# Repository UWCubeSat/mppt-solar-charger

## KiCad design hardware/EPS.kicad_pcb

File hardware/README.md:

# MPPTSolarCharger

A Maximum Power Point Tracking battery charger circuit for testing solar panels and developing efficient battery management systems.

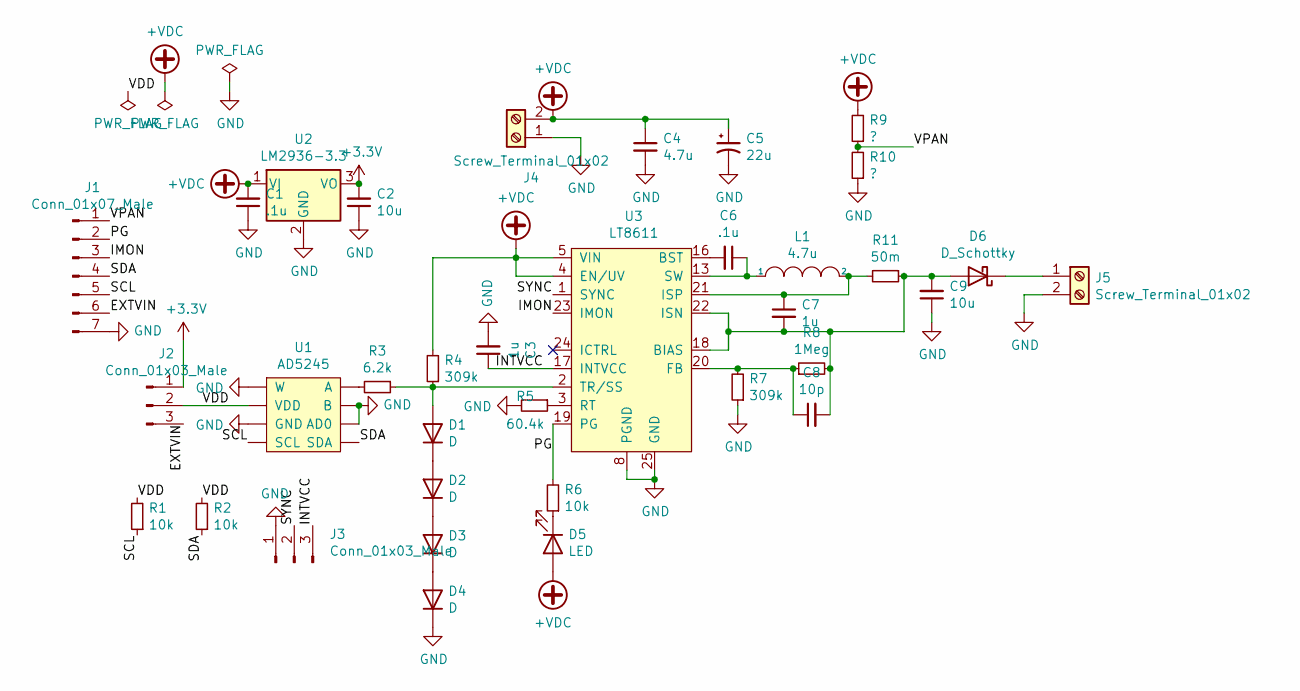
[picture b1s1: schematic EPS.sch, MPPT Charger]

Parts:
C1, C6: .1u; C_0805_2012Metric_Pad1.15x1.40mm_HandSolder
C2, C9: 10u; C_0805_2012Metric_Pad1.15x1.40mm_HandSolder
C3, C7: 1u; C_0805_2012Metric_Pad1.15x1.40mm_HandSolder
C4: 4.7u; C_0805_2012Metric_Pad1.15x1.40mm_HandSolder
C5: 22u; CP_Radial_D6.3mm_P2.50mm
C8: 10p; C_0805_2012Metric_Pad1.15x1.40mm_HandSolder
D1, D2, D3, D4: D; D_SOD-123
D5: LED; LED_0805_2012Metric_Pad1.15x1.40mm_HandSolder
D6: D_Schottky; D_SOD-128
J1: Conn_01x07_Male; PinHeader_1x07_P2.54mm_Vertical
J2, J3: Conn_01x03_Male; PinHeader_1x03_P2.54mm_Vertical
J4, J5: Screw_Terminal_01x02; TerminalBlock_Phoenix_PT-1,5-2-3.5-H_1x02_P3.50mm_Horizontal
L1: 4.7u; BWVS00606045
R1, R2, R6: 10k; R_0805_2012Metric_Pad1.15x1.40mm_HandSolder
R3: 6.2k; R_0805_2012Metric_Pad1.15x1.40mm_HandSolder
R4, R7: 309k; R_0805_2012Metric_Pad1.15x1.40mm_HandSolder
R5: 60.4k; R_0805_2012Metric_Pad1.15x1.40mm_HandSolder
R8: 1Meg; R_0805_2012Metric_Pad1.15x1.40mm_HandSolder
R9, R10: ?; R_0805_2012Metric_Pad1.15x1.40mm_HandSolder
R11: 50m; R_2512_6332Metric_Pad1.52x3.35mm_HandSolder
U1: AD5245; SOT-23-8
U2: LM2936-3.3; SOT-223-3_TabPin2
U3: LT8611; 24-QFN_3x5

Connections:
+3V3: C2.2, J2.1, U2.3 (VO)
+VDC: C1.2, C4.1, C5.1, D5.2 (A), J4.2, R4.2, R9.2, U2.1 (VI), U3.4 (EN/UV), U3.5 (VIN), U3.6 (VIN)
/EXTVIN: J1.6, J2.3
/IMON: J1.3, U3.23 (IMON)
/INTVCC: C3.1, J3.3, U3.17 (INTVCC)
/PG: J1.2, R6.2, U3.19 (PG)
/SCL: J1.5, R1.1, U1.4 (SCL)
/SDA: J1.4, R2.1, U1.5 (SDA)
/SYNC: J3.2, U3.1 (SYNC)
/VDD: J2.2, R1.2, R2.2, U1.2 (VDD)
/VPAN: J1.1, R9.1, R10.2
GND: C1.1, C2.1, C3.2, C4.2, C5.2, C9.1, D4.1 (K), J1.7, J3.1, J4.1, J5.2, R5.2, R7.1, R10.1, U1.1 (W), U1.3 (GND), U1.6 (AD0), U1.7 (B), U2.2 (GND), U3.7 (PGND), U3.8 (PGND), U3.9 (NC), U3.10 (NC), U3.11 (NC), U3.12 (NC), U3.25 (GND)
unnamed: C6.1, L1.1, U3.13 (SW), U3.14 (SW), U3.15 (SW)
unnamed: C6.2, U3.16 (BST)
unnamed: C7.1, L1.2, R11.2, U3.21 (ISP)
unnamed: C7.2, C8.2, C9.2, D6.2 (A), R8.2, R11.1, U3.18 (BIAS), U3.22 (ISN)
unnamed: C8.1, R7.2, R8.1, U3.20 (FB)
unnamed: D1.1 (K), D2.2 (A)
unnamed: D1.2 (A), R3.1, R4.1, U3.2 (TR/SS)
unnamed: D2.1 (K), D3.2 (A)
unnamed: D3.1 (K), D4.2 (A)
unnamed: D5.1 (K), R6.1
unnamed: D6.1 (K), J5.1
unnamed: R3.2, U1.8 (A)
unnamed: R5.1, U3.3 (RT)

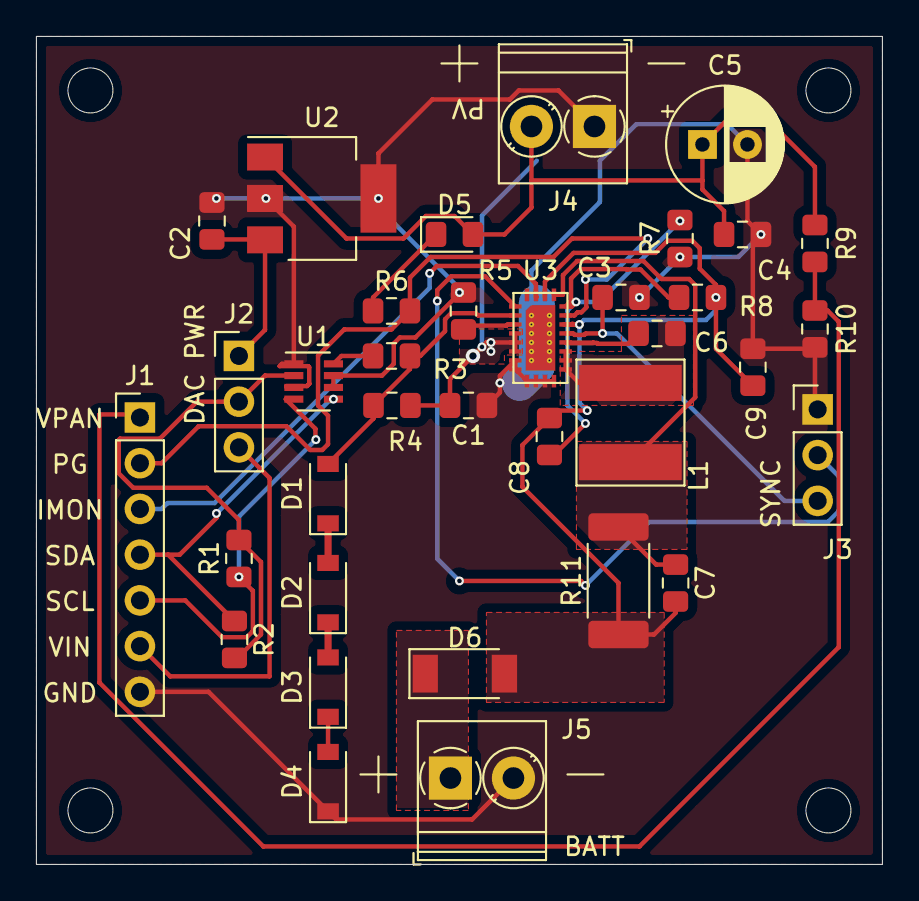
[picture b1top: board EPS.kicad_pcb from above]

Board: 2 copper layers, 47.0 x 46.0 mm, 35 parts (0 on the bottom side), 25 nets.

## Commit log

2020-11-28 Added LT8611 MPPT Eval Schematic
2020-11-28 Rename MTTP.asc to MPPT.asc
2020-11-28 Modified schematic to pass electrical rules check
    Added power flags. Resolved error due to stacked power output pins
2020-11-29 PCB Board Layout Created
2020-11-30 Updated .pro file, PCB Layout
2020-11-30 Tweaked polygons and silkscreen
2020-12-19 Rename EPS-cache.lib to hardware/EPS-cache.lib
2020-12-19 Rename EPS.kicad_pcb to hardware/EPS.kicad_pcb
2020-12-19 Rename EPS.kicad_pcb-bak to hardware/EPS.kicad_pcb-bak
2020-12-19 Rename EPS.pro to hardware/EPS.pro
2020-12-19 Rename EPS.sch to hardware/EPS.sch
2020-12-19 Rename EPS.sch-bak to hardware/EPS.sch-bak
2020-12-19 Rename README.md to hardware/README.md
2020-12-19 Rename fp-info-cache to hardware/fp-info-cache
2020-12-19 Rename readme to arduino/readme
2021-01-13 Rename arduino/I2C_AD5245_ESP32Test.ino to arduino/I2C_AD5245_ESP32Test/I2C_AD5245_ESP32Test.ino
2021-01-13 Rename arduino/Scan_I2C_Address.ino to arduino/Scan_I2C_Address/Scan_I2C_Address.ino
2021-01-13 Rename arduino/Scan_I2C_Address2.ino to arduino/Scan_I2C_Address2/Scan_I2C_Address2.ino
2021-03-04 Potential output circuit with boost converter, load switch, and power monitor.
    Schematic for 5v output, should be able to provide ~1A current
2023-02-11 Added gerber and drill files for MPPT
